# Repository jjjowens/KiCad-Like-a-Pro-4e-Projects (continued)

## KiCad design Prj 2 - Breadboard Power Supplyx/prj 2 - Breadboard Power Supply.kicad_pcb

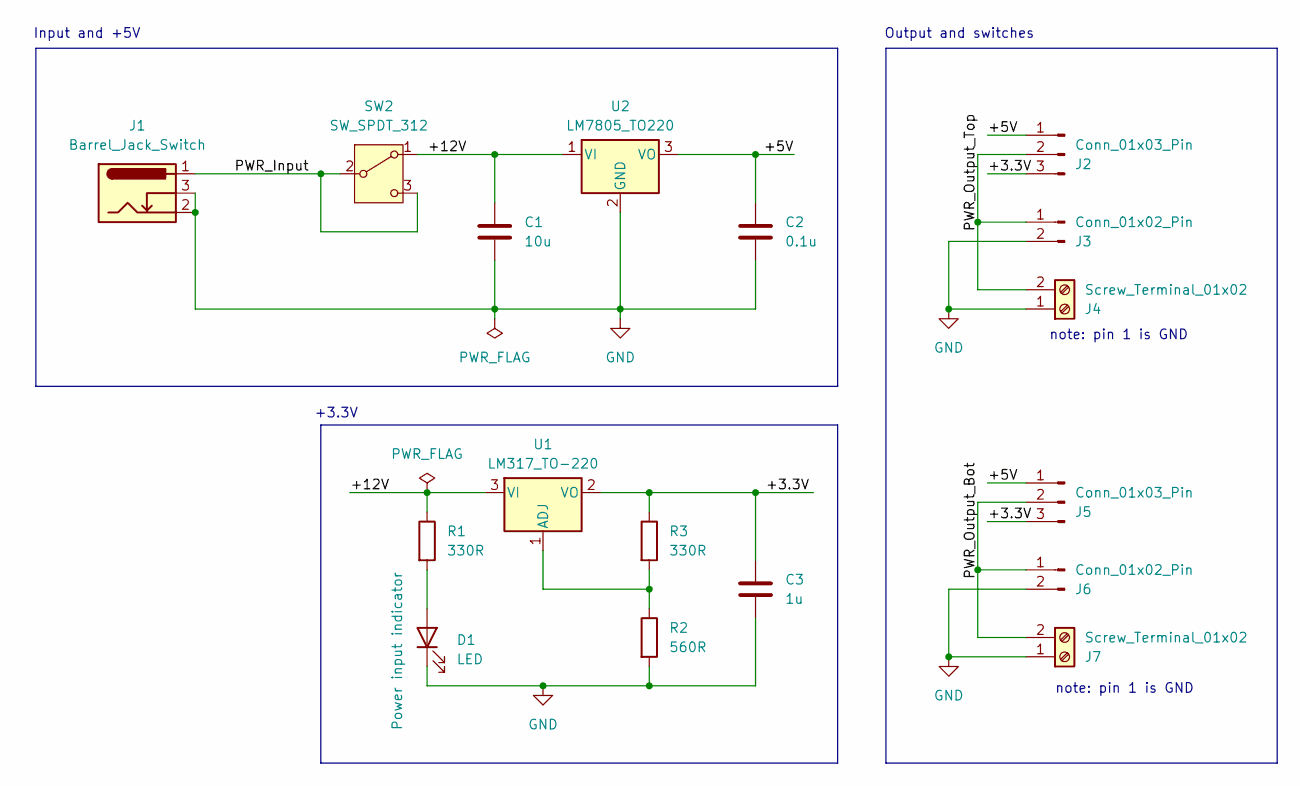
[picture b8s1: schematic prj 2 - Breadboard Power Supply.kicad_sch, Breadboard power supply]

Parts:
C1: 10u; C_Disc_D3.0mm_W1.6mm_P2.50mm
C2: 0.1u; C_Disc_D3.0mm_W1.6mm_P2.50mm
C3: 1u; C_Disc_D3.0mm_W1.6mm_P2.50mm
D1: LED; LED_D5.0mm
J1: Barrel_Jack_Switch; BarrelJack_Horizontal
J2, J5: Conn_01x03_Pin; PinHeader_1x03_P2.54mm_Vertical
J3, J6: Conn_01x02_Pin; PinHeader_1x02_P2.54mm_Vertical
J4, J7: Screw_Terminal_01x02; TerminalBlock_bornier-2_P5.08mm
R1, R3: 330R; R_Axial_DIN0204_L3.6mm_D1.6mm_P7.62mm_Horizontal
R2: 560R; R_Axial_DIN0204_L3.6mm_D1.6mm_P7.62mm_Horizontal
SW2: SW_SPDT_312; SW_1218_EWI
U1: LM317_TO-220; TO-220-3_Vertical
U2: LM7805_TO220; TO-220-3_Vertical

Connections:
/+3.3V: C3.1, J2.3, J5.3, R3.1, U1.2 (VO)
/+5V: C2.1, J2.1, J5.1, U2.3 (VO)
/+12V: C1.1, R1.1, SW2.1 (A), U1.3 (VI), U2.1 (VI)
/PWR_Input: J1.1, SW2.2 (B), SW2.3 (C)
/PWR_Output_Bot: J5.2, J6.1, J7.2
/PWR_Output_Top: J2.2, J3.1, J4.2
GND: C1.2, C2.2, C3.2, D1.1 (K), J1.2, J1.3, J3.2, J4.1, J6.2, J7.1, R2.2, U2.2 (GND)
unnamed: D1.2 (A), R1.2
unnamed: R2.1, R3.2, U1.1 (ADJ)

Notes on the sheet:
+3.3V
note: pin 1 is GND
Input and +5V
Output and switches

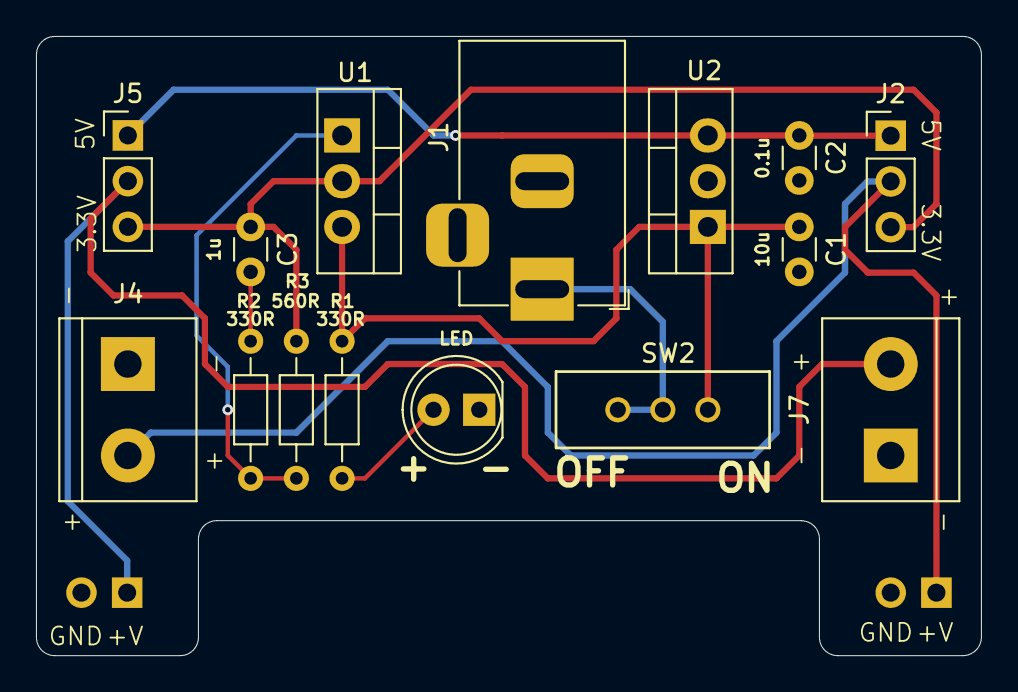
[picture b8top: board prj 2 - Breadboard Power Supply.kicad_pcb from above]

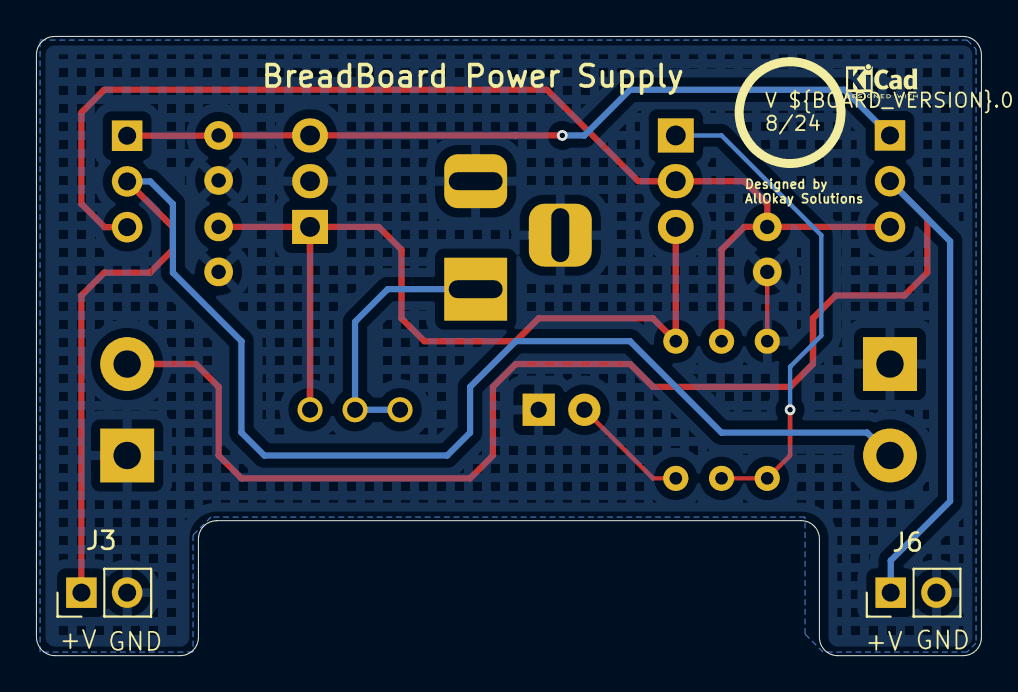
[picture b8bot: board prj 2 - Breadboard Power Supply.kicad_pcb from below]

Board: 2 copper layers, 52.5 x 34.4 mm, 17 parts (2 on the bottom side), 9 nets.

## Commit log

2024-09-07 Repositioned modules in schematics
    modified: Prj 4 - 4x8x4 Matrix Clock/Prj 4 - 4x8x4 Matrix Clock.kicad_sch
2024-09-07 Moved Vcc Message
2024-09-07 Corrected lower case in folder name
2024-09-07 Renaming folder
2024-09-07 deleted unnecessary files
2024-09-07 Update Prj 4 - 4x8x4 Matrix Clock.kicad_sch
    Update text for git test
2024-09-07 Update Prj 4 - 4x8x4 Matrix Clock.kicad_sch
    Removed BLIP!
2024-09-07 Update Prj 4 - 4x8x4 Matrix Clock.kicad_sch
    Fixed typo
2024-09-07 Test
2024-09-07 Properties, Schematics and Page setup
2024-09-07 +Custom components and loaded symbols
2024-09-07 +hierarchical sheet
2024-09-07 wired first main sheet
2024-09-07 Complete wiring, ERC Clean
2024-09-07 PCBEditor environment setup
2024-09-07 Associated footprints
2024-09-07 setup layout parameters
2024-09-08 distributed components and initial layout
2024-09-08 Pausing, need fix on schecmatics
2024-09-08 Separated SCL and SCK
2024-09-08 Separated SCL and SCK again
2024-09-08 I2c and SPI Nets
2024-09-09 Completed routing, pending further improvements
2024-09-09 v0.1 Complete, ready for manuf
2024-09-09 Adjusted Cu2Edge for PCBWay
2024-09-09 Completed 4-layer routing
2024-09-09 Added Keepout zones for the mounting holes
2024-09-10 Added label to AREF net
2024-09-10 added .gitattributes
2024-09-10 Added net /AREF
2024-09-11 Added Prj 6 - ESP Clone DevKit
2024-09-11 Completed most of PCB Editor parameters and constrais
2024-09-13 Trying to do differential tracks
2024-09-15 Completed routing v0.1
2024-09-16 Completed all projects in book, this is the final commit
